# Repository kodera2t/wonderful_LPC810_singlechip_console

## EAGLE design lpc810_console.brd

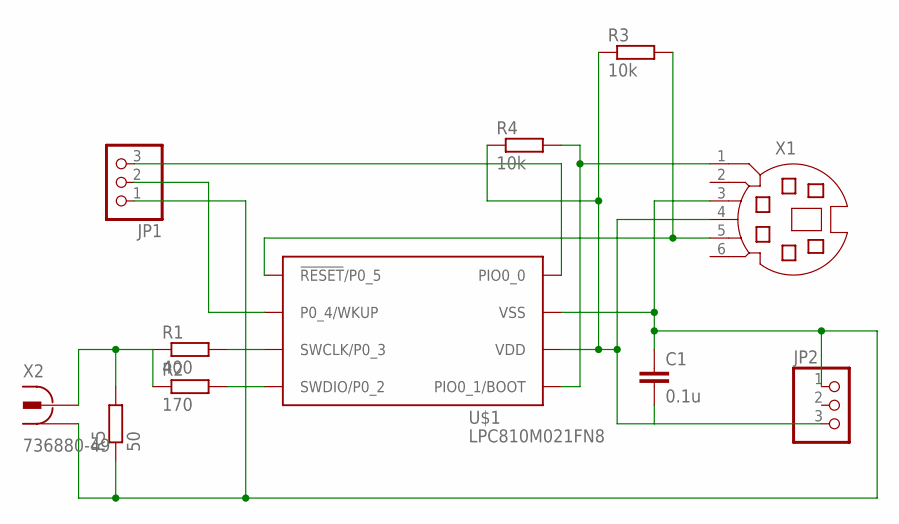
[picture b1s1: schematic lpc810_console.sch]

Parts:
C1: 0.1u; C0603
JP1, JP2: PINHD-1X3; 1X03
R1: 400; R0603
R2: 170; R0603
R3, R4: 10k; R0603
R5: 50; R0603
U$1: LPC810M021FN8; DIP8
X1: MD06S; MDIN06S
X2: 736880-49

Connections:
unnamed: JP1.2, U$1.P$2 (P0_4/WKUP)
unnamed: C1.2, JP2.3, R3.1, R4.1, U$1.P$6 (VDD), X1.4
unnamed: R4.2, U$1.P$5 (PIO0_1/BOOT), X1.1
unnamed: R3.2, U$1.P$1 (!RESET!/P0_5), X1.5
unnamed: JP1.3, U$1.P$8 (PIO0_0)
unnamed: R1.2, U$1.P$3 (SWCLK/P0_3)
unnamed: R2.2, U$1.P$4 (SWDIO/P0_2)
unnamed: R1.1, R2.1, R5.2, X2.2
unnamed: C1.1, JP1.1, JP2.1, R5.1, U$1.P$7 (VSS), X1.3, X2.1, X2.1@1 (1), X2.1@2 (1)

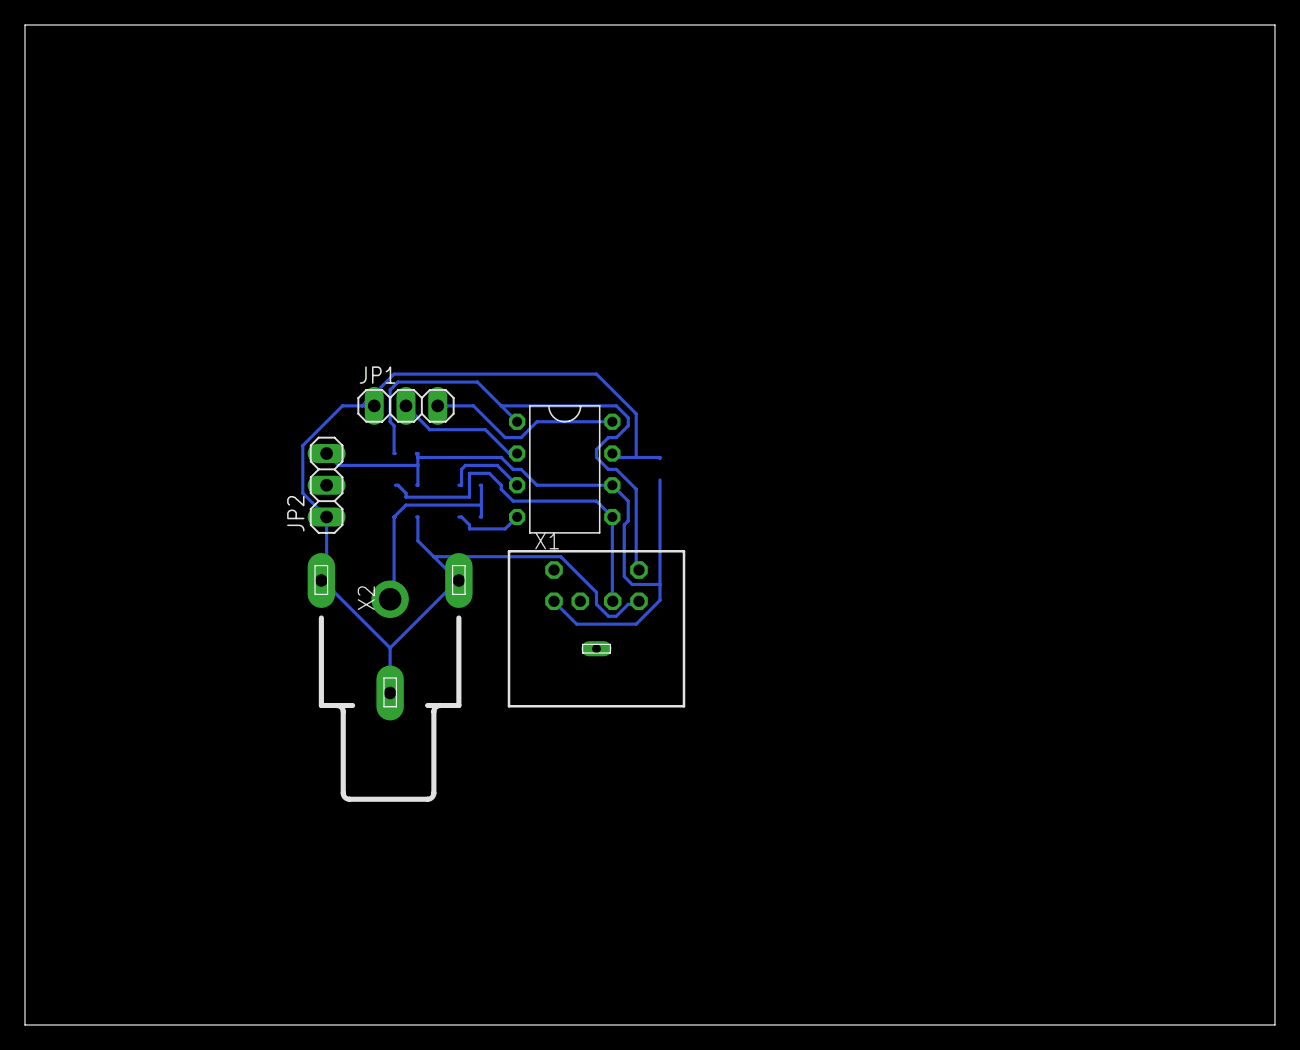
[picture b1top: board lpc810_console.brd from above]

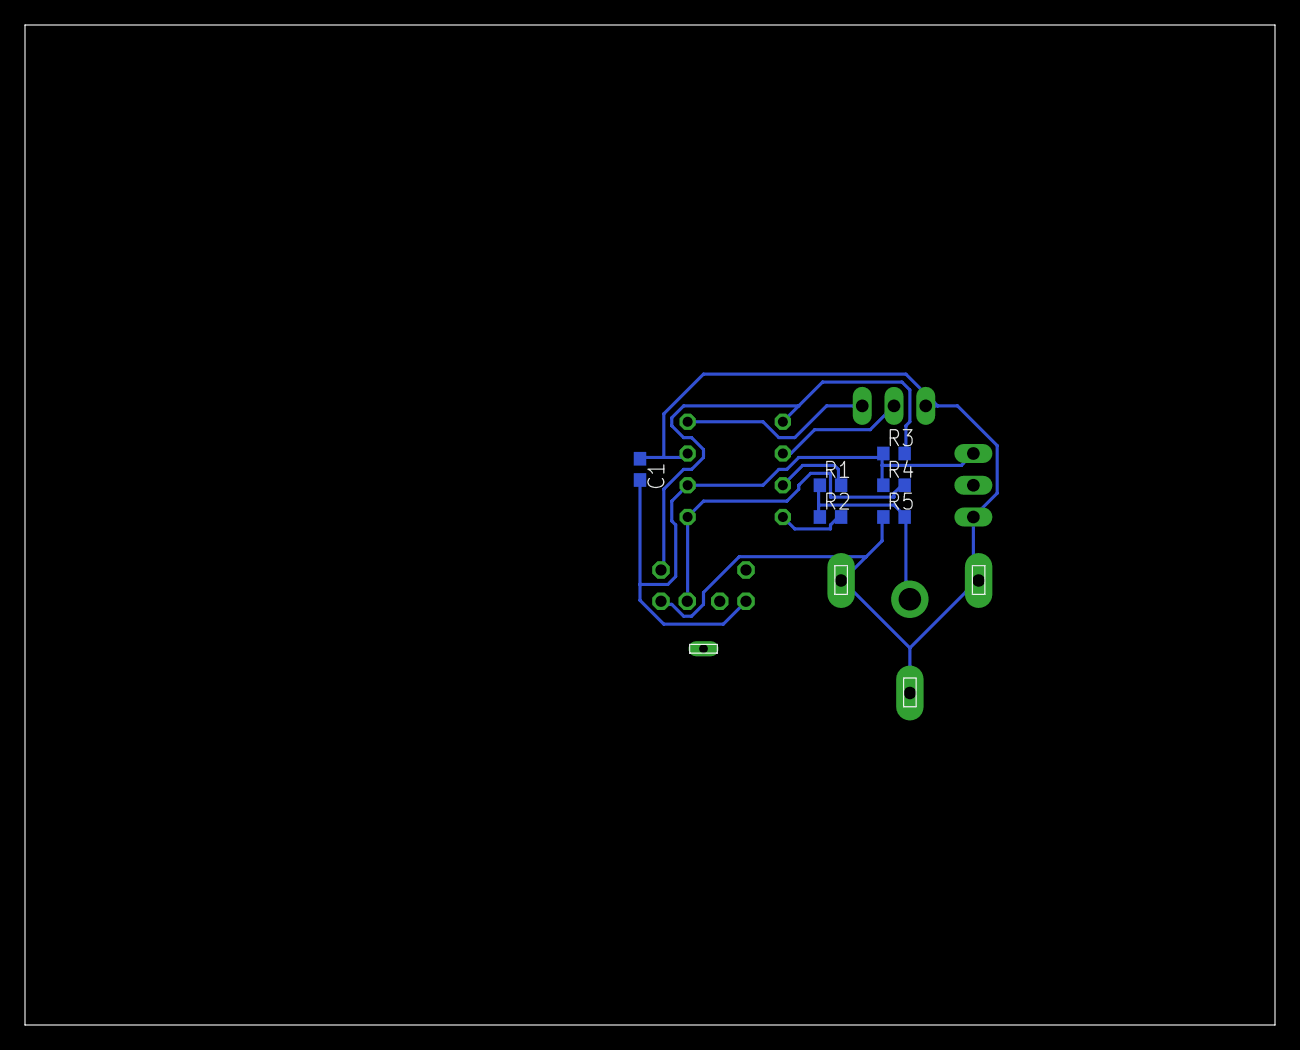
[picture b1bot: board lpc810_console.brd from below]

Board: 2 copper layers, 100.0 x 80.0 mm, 11 parts (6 on the bottom side), 9 nets.

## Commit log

2015-05-29 initial submission, just board files only
